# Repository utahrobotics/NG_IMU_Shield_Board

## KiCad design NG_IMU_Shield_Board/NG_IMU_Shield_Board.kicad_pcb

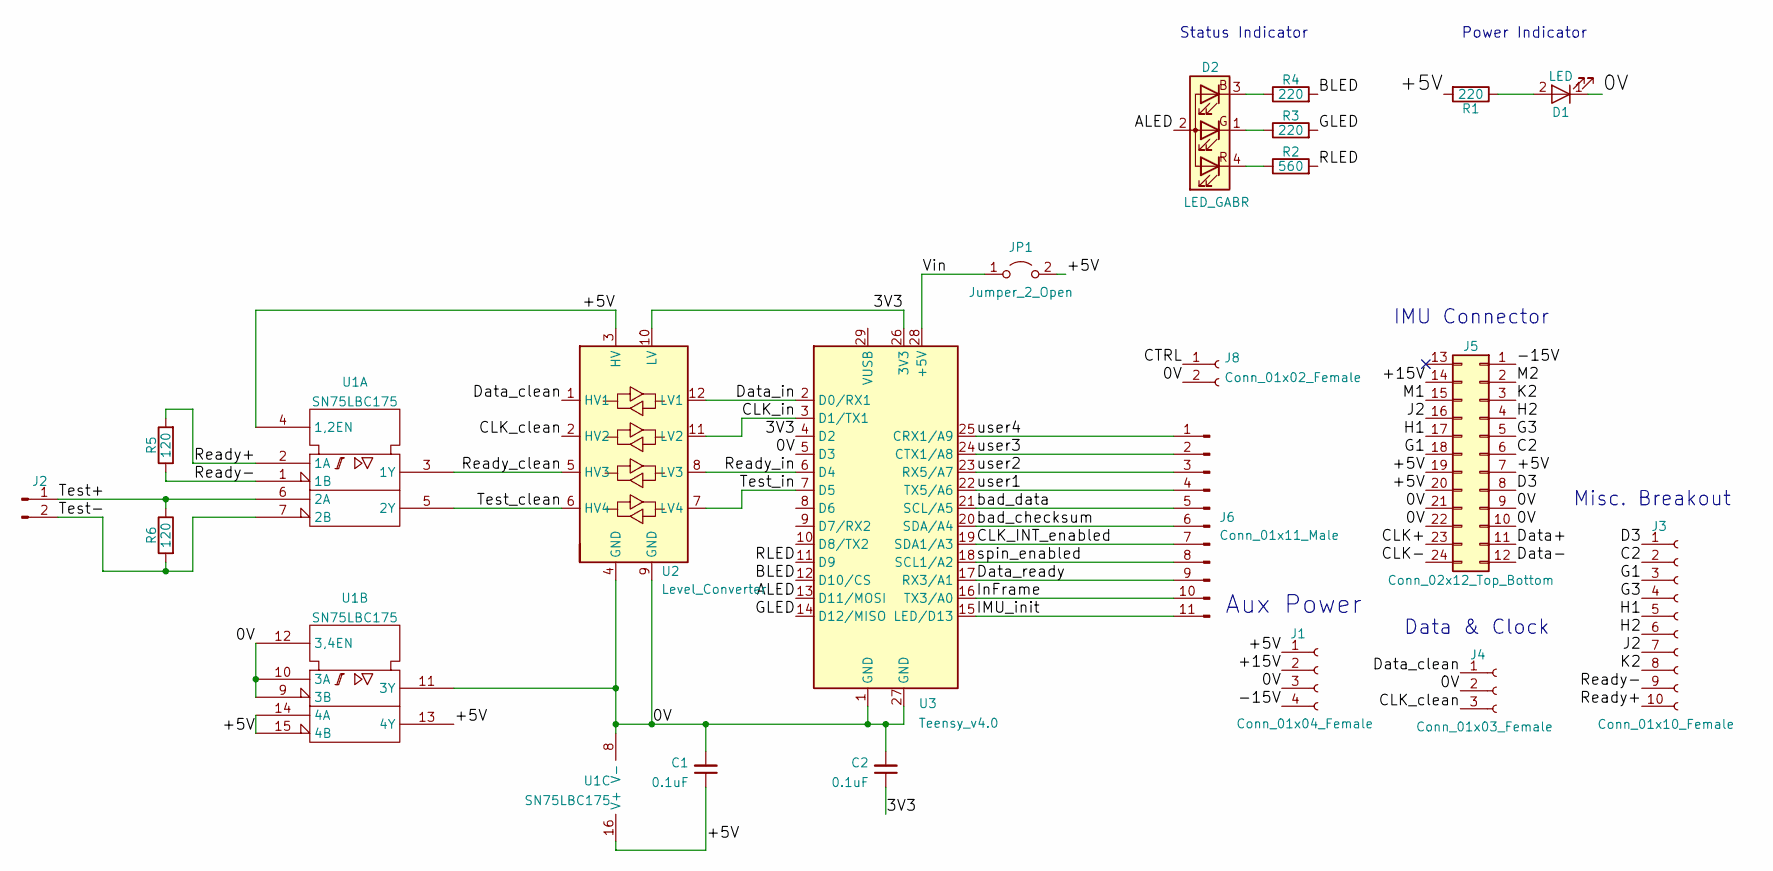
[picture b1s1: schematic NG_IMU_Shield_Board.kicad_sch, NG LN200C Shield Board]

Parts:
C1, C2: 0.1uF; C_Disc_D3.0mm_W1.6mm_P2.50mm
D1: LED; LED_D5.0mm
D2: LED_GABR; LED_D5.0mm-4_RGB
J1: Conn_01x04_Female; PinSocket_1x04_P2.54mm_Vertical
J2: Conn_01x02_Male; PinHeader_1x02_P2.54mm_Vertical
J3: Conn_01x10_Female; PinSocket_1x10_P2.54mm_Vertical
J4: Conn_01x03_Female; PinSocket_1x03_P2.54mm_Vertical
J5: Conn_02x12_Top_Bottom; IPL1-112-01-F-D-K
J6: Conn_01x11_Male; PinHeader_1x11_P2.54mm_Vertical
J8: Conn_01x02_Female; PinSocket_1x02_P2.54mm_Vertical
JP1: Jumper_2_Open; PinHeader_1x02_P2.54mm_Vertical
R1: 220; R_1206_3216Metric_Pad1.30x1.75mm_HandSolder
R2: 560; R_0805_2012Metric_Pad1.20x1.40mm_HandSolder
R3, R4: 220; R_0805_2012Metric_Pad1.20x1.40mm_HandSolder
R5, R6: 120; R_1206_3216Metric_Pad1.30x1.75mm_HandSolder
U1: SN75LBC175; SOIC-16_3.9x9.9mm_P1.27mm
U2: Level_Converter
U3: Teensy_v4.0; Teensy4.0

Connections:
/0V: C1.2, C2.2, D1.1 (K), J1.3, J4.2, J5.9, J5.10, J5.21, J5.22, J8.2, U1.8 (V-), U1.9 (3B), U1.10 (3A), U1.11 (3Y), U1.12 (3,4EN), U2.4 (GND), U2.9 (GND), U3.1 (GND), U3.5 (D3), U3.27 (GND)
/3V3: C2.1, U2.10 (LV), U3.4 (D2), U3.26 (3V3)
/+5V: C1.1, J1.1, J5.7, J5.19, J5.20, JP1.2 (B), R1.2, U1.4 (1,2EN), U1.13 (4Y), U1.14 (4A), U1.15 (4B), U1.16 (V+), U2.3 (HV)
/+15V: J1.2, J5.14
/-15V: J1.4, J5.1
/ALED: D2.2 (A), U3.13 (D11/MOSI)
/BLED: R4.2, U3.12 (D10/CS)
/C2: J3.2, J5.6
/CLK_INT_enabled: J6.7, U3.19 (SDA1/A3)
/CLK_clean: J4.3, U2.2 (HV2)
/CLK_in: U2.11 (LV2), U3.3 (D1/TX1)
/CTRL: J8.1
/D3: J3.1, J5.8
/Data_clean: J4.1, U2.1 (HV1)
/Data_in: U2.12 (LV1), U3.2 (D0/RX1)
/Data_ready: J6.9, U3.17 (RX3/A1)
/G1: J3.3, J5.18
/G3: J3.4, J5.5
/GLED: R3.2, U3.14 (D12/MISO)
/H1: J3.5, J5.17
/H2: J3.6, J5.4
/IMU_init: J6.11, U3.15 (LED/D13)
/InFrame: J6.10, U3.16 (TX3/A0)
/J2: J3.7, J5.16
/K2: J3.8, J5.3
/RLED: R2.2, U3.11 (D9)
/Ready+: J3.10, R5.2, U1.2 (1A)
/Ready-: J3.9, R5.1, U1.1 (1B)
/Ready_clean: U1.3 (1Y), U2.5 (HV3)
/Ready_in: U2.8 (LV3), U3.6 (D4)
/Test+: J2.1, R6.1, U1.6 (2A)
/Test-: J2.2, R6.2, U1.7 (2B)
/Test_clean: U1.5 (2Y), U2.6 (HV4)
/Test_in: U2.7 (LV4), U3.7 (D5)
/Vin: JP1.1 (A), U3.28 (+5V)
/bad_checksum: J6.6, U3.20 (SDA/A4)
/bad_data: J6.5, U3.21 (SCL/A5)
/spin_enabled: J6.8, U3.18 (SCL1/A2)
/user1: J6.4, U3.22 (TX5/A6)
/user2: J6.3, U3.23 (RX5/A7)
/user3: J6.2, U3.24 (CTX1/A8)
/user4: J6.1, U3.25 (CRX1/A9)
unnamed: D1.2 (A), R1.1
unnamed: D2.1 (GK), R3.1
unnamed: D2.3 (BK), R4.1
unnamed: D2.4 (RK), R2.1

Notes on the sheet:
Data & Clock
IMU Connector
Misc. Breakout
Aux Power
Status Indicator
Power Indicator

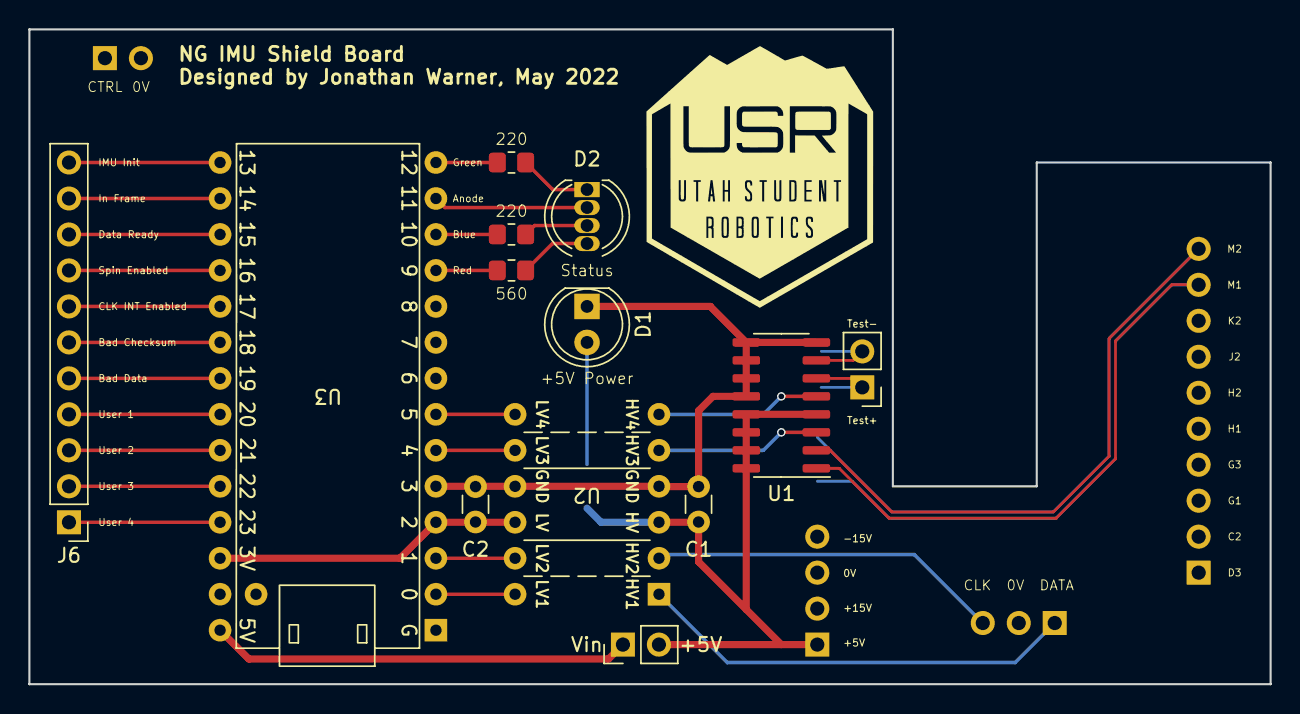
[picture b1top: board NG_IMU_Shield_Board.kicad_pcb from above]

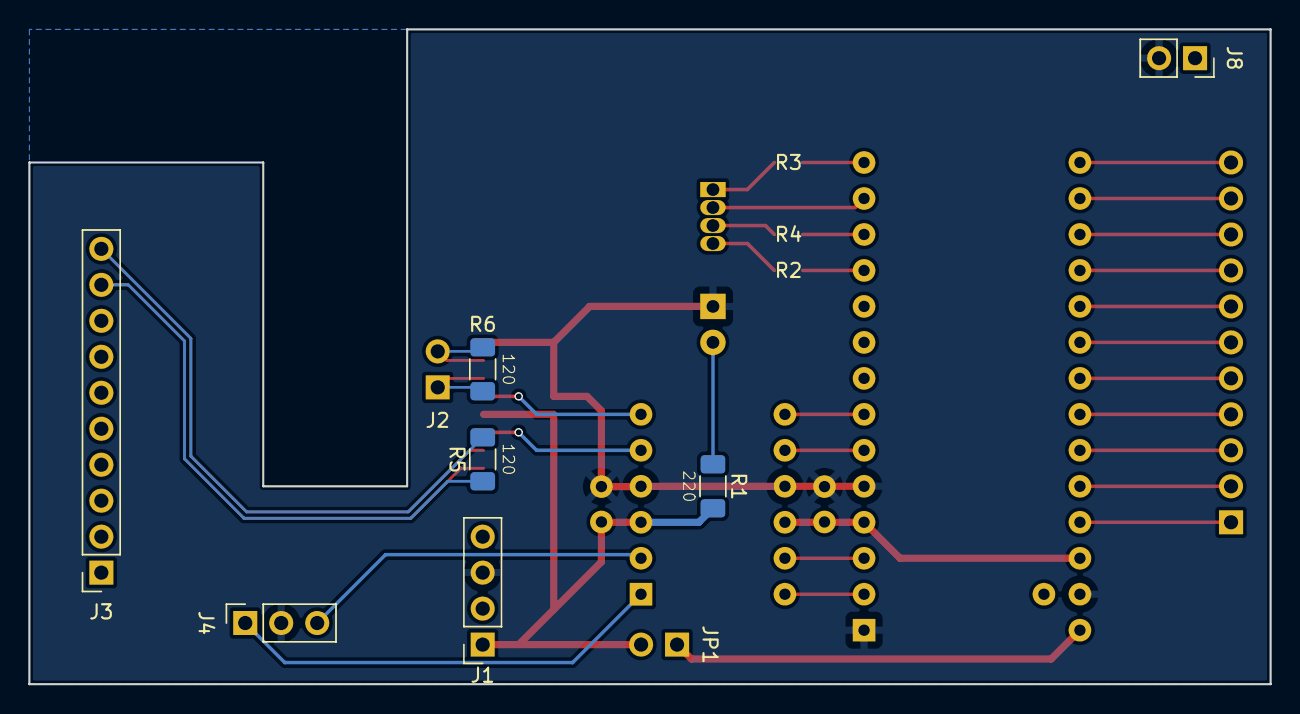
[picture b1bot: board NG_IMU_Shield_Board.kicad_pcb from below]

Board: 2 copper layers, 87.6 x 46.2 mm, 20 parts (7 on the bottom side), 35 nets.

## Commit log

2022-05-19 Changed to use LM393 and completed schematic
2022-05-31 Simplified and updated footprints to ease routing
2022-05-31 Finished routing board
2022-05-31 Added signal names, level shifter sockets, and small fix
2022-06-01 Moved status LED, added more user signals, other improvements
2022-06-01 Added datasheets/etc. and cleanup
2022-06-01 Small fixes
2022-06-01 Added BOM and Gerber files
2022-06-02 Moved board to match original coordinates, added CTRL, and minor changes
2022-06-02 Added pin socket to allow disabling power with a jumper
2022-06-02 Updated 3D models
